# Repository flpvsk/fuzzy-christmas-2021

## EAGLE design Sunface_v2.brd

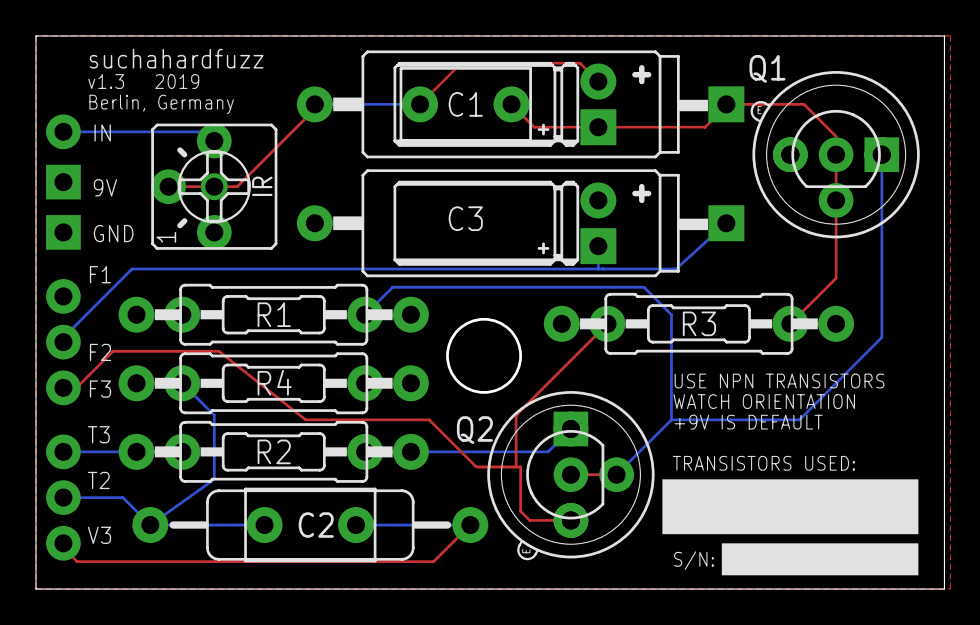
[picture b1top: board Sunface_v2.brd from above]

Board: 2 copper layers, 50.3 x 30.6 mm, 29 parts (0 on the bottom side), 12 nets.

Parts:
C1: 1uF; 050.AXIAL
C1_, C5: 050.FLAT
C1__, C2_: BOX_MED
C2: 0.01uF; AXIAL
C3: 22uF; 050.AXIAL
GND: PADS.SQR_NL; PAD4
IR: 50k; TRIM1
Q1, Q2: GE NPN; TO-5
Q3, Q4: 2N5088; TO92
R1: 33k; 0.4"
R2: 2.2k; 0.4"
R3: 100k; 0.4"
R4: 470R; 0.4"
R5, R6, R7, R8: 0.6"
U$1, U$2, U$3, U$4, U$5, U$6, U$7: PADS.RND_NL; PAD2
U$8: PADS.SQR_NL; PAD4

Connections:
+9V: R1.2, R4.2, R5.2, R8.2, U$8.P$1
GND: C3.-, C5.-, GND.P$1, IR.1, Q1.1, Q3.3, U$7.P$1
unnamed: C1.-, C1_.-, C1__.1, IR.2
unnamed: C1.+, C1_.+, C1__.2, Q1.2, Q3.2, R3.2, R7.2
unnamed: Q1.3, Q2.2, Q3.1, Q4.2, R1.1, R5.1
unnamed: R2.2, R6.2, U$3.P$1
unnamed: Q2.3, Q4.1, R2.1, R6.1
unnamed: Q2.1, Q4.3, R3.1, R7.1, U$5.P$1
unnamed: C3.+, C5.+, U$6.P$1
unnamed: IR.3, U$1.P$1
unnamed: C2.1, C2_.1, R4.1, R8.1, U$4.P$1
OUT: C2.2, C2_.2, U$2.P$1

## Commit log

2020-11-21 Init
